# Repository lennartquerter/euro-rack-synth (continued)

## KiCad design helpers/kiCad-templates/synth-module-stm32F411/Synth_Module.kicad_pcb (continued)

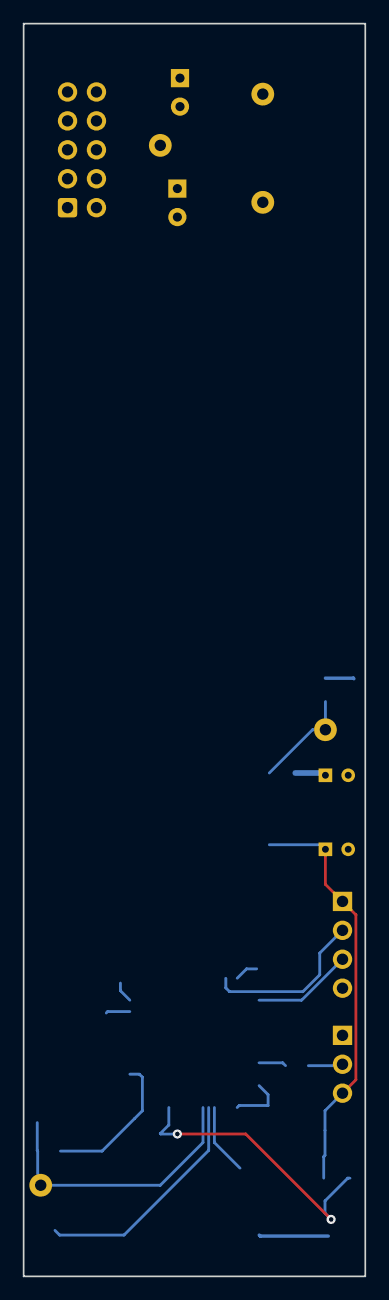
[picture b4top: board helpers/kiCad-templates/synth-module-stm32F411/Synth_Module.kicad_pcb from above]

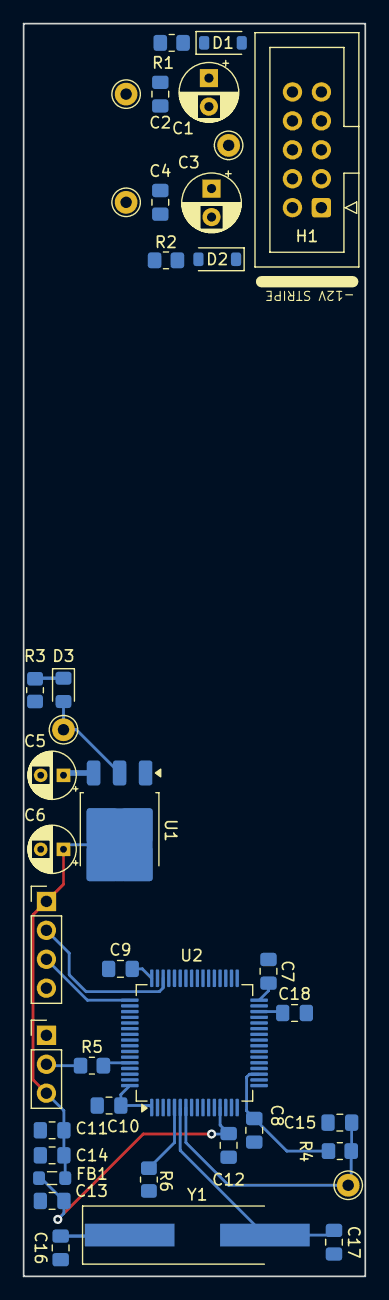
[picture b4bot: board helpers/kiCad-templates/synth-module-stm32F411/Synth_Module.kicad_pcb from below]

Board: 2 copper layers, 30.0 x 110.0 mm, 39 parts (39 on the bottom side), 19 nets.

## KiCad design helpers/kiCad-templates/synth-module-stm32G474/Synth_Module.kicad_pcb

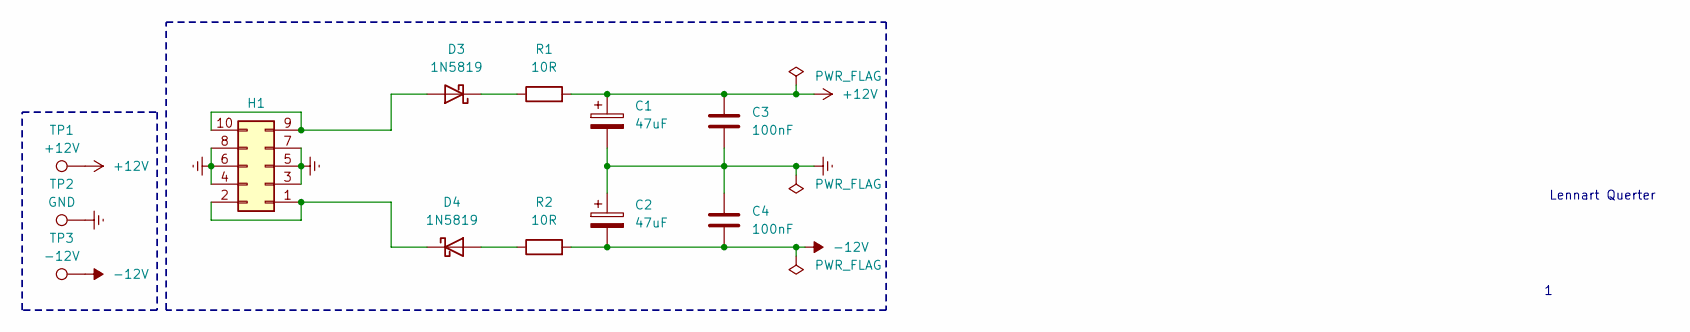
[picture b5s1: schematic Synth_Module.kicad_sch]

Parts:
C1, C2: 47uF; CP_Radial_D6.3mm_P2.50mm
C3, C4: 100nF; C_Disc_D5.0mm_W2.5mm_P5.00mm
D3, D4: 1N5819; D_DO-41_SOD81_P10.16mm_Horizontal
H1: Conn_02x05_PWR_Eurorack; IDC-Header_2x05_P2.54mm_Vertical
R1, R2: 10R; R_Axial_DIN0207_L6.3mm_D2.5mm_P7.62mm_Horizontal
TP1: +12V; Pin_D1.0mm_L10.0mm
TP2: GND; Pin_D1.0mm_L10.0mm
TP3: -12V; Pin_D1.0mm_L10.0mm

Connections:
+12V: C1.1, C3.1, R1.2, TP1.1
-12V: C2.2, C4.2, R2.2, TP3.1
GNDREF: C1.2, C2.1, C3.2, C4.1, H1.3, H1.4, H1.5, H1.6, H1.7, H1.8, TP2.1
unnamed: D3.2 (A), H1.9, H1.10
unnamed: D3.1 (K), R1.1
unnamed: D4.2 (A), R2.1
unnamed: D4.1 (K), H1.1, H1.2

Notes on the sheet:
Lennart Querter

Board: 2 copper layers, 12 parts (0 on the bottom side), 7 nets, no tracks yet.

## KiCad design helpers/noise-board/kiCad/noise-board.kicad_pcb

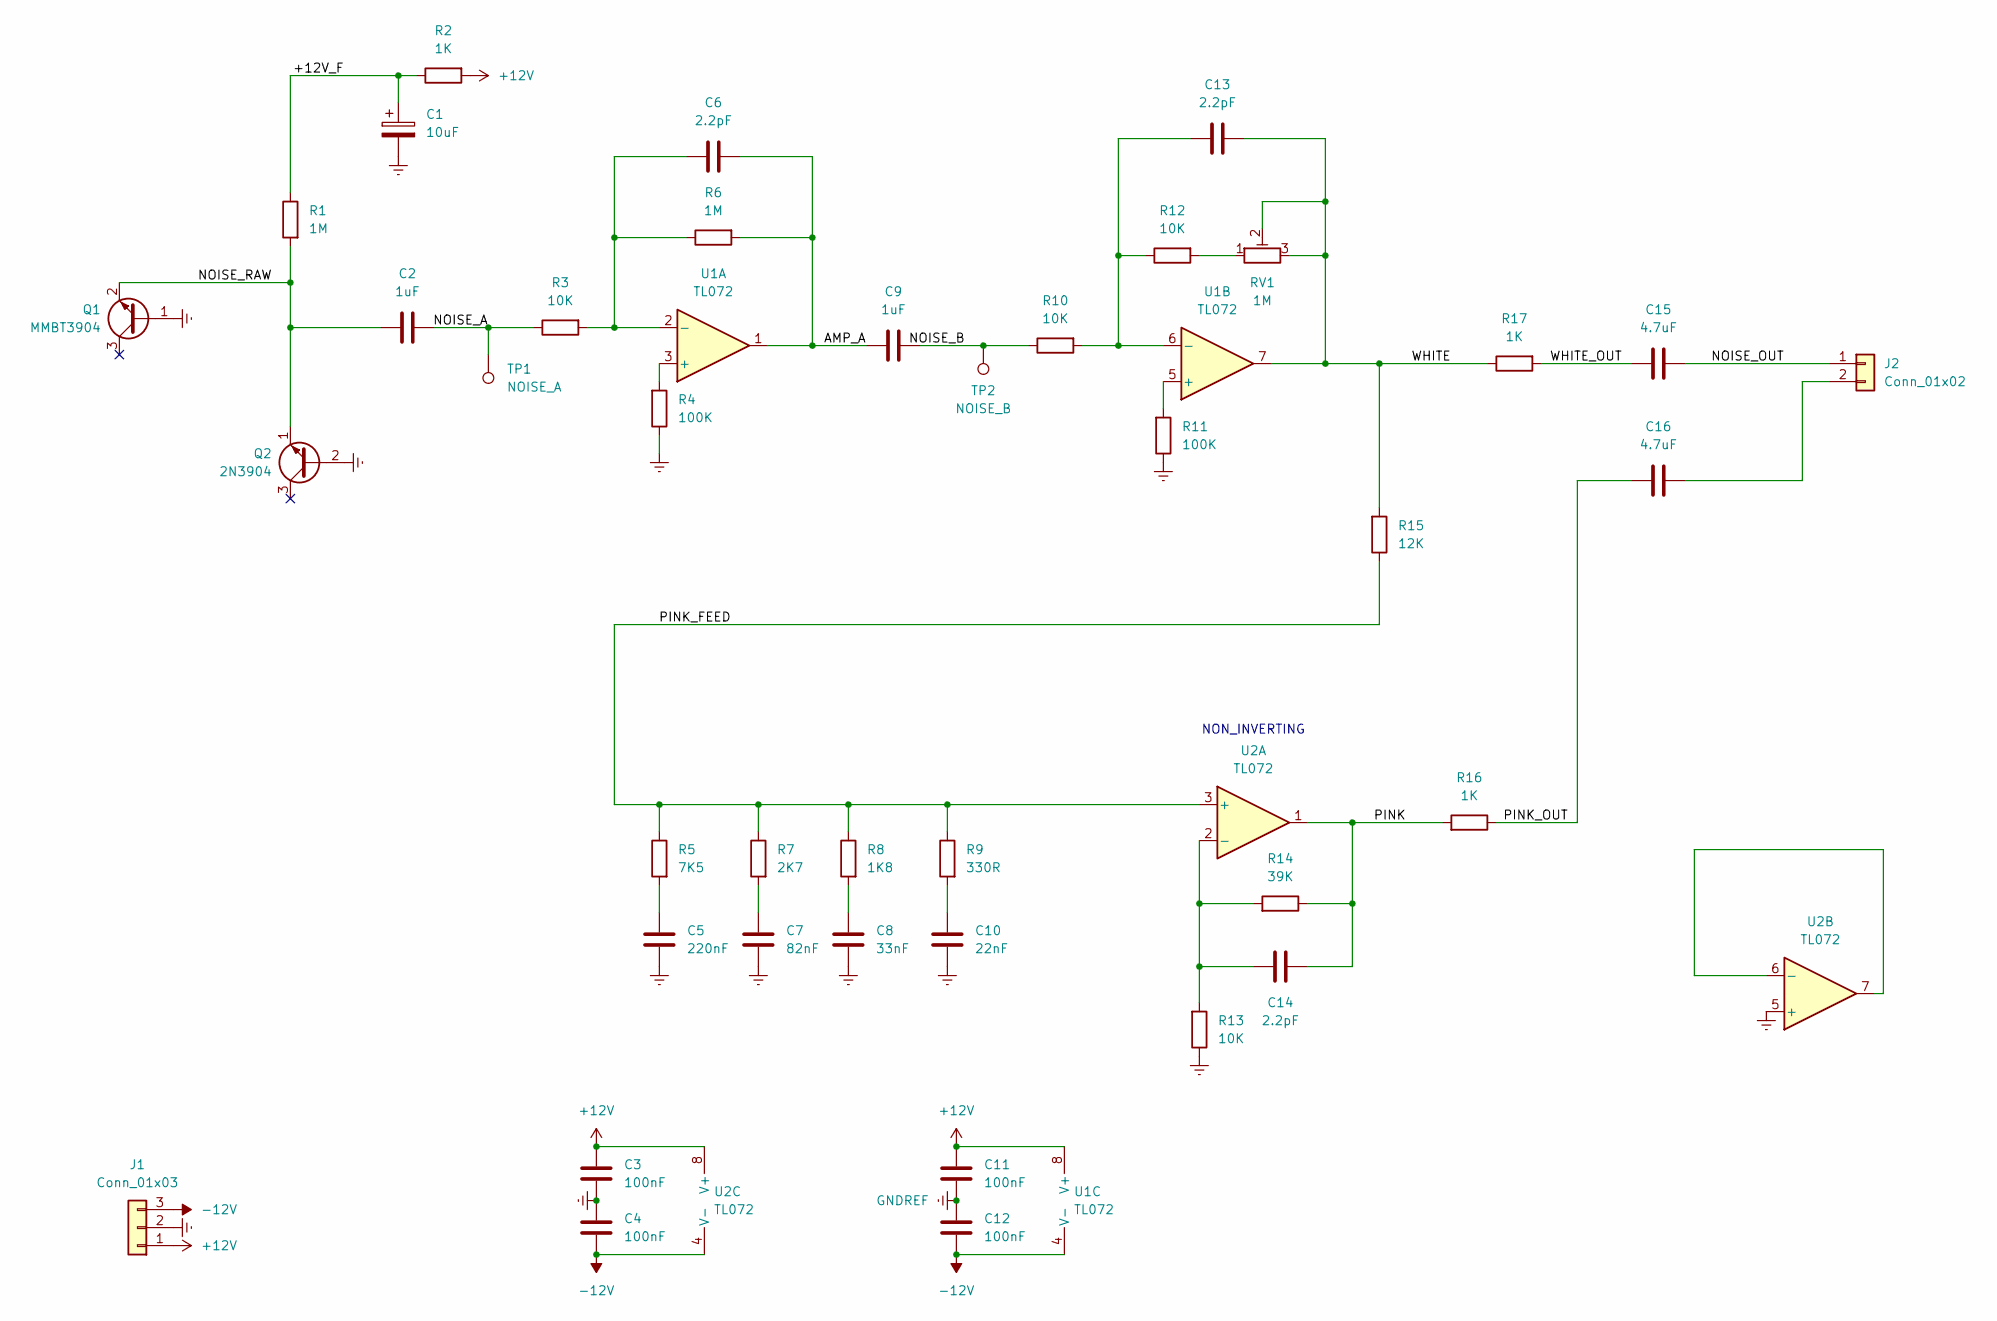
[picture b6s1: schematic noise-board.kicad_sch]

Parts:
C1: 10uF; CP_Radial_D4.0mm_P2.00mm
C2, C9: 1uF; C_0805_2012Metric_Pad1.18x1.45mm_HandSolder
C3, C4, C11, C12: 100nF; C_0805_2012Metric_Pad1.18x1.45mm_HandSolder
C5: 220nF; C_0805_2012Metric_Pad1.18x1.45mm_HandSolder
C6, C13, C14: 2.2pF; C_0805_2012Metric_Pad1.18x1.45mm_HandSolder
C7: 82nF; C_0805_2012Metric_Pad1.18x1.45mm_HandSolder
C8: 33nF; C_0805_2012Metric_Pad1.18x1.45mm_HandSolder
C10: 22nF; C_0805_2012Metric_Pad1.18x1.45mm_HandSolder
C15, C16: 4.7uF; C_0805_2012Metric_Pad1.18x1.45mm_HandSolder
J1: Conn_01x03; PinHeader_1x03_P2.54mm_Vertical
J2: Conn_01x02; PinSocket_1x02_P2.54mm_Vertical
Q1: MMBT3904; SOT-23
Q2: 2N3904; TO-92_HandSolder
R1, R6: 1M; R_0805_2012Metric_Pad1.20x1.40mm_HandSolder
R2, R16, R17: 1K; R_0805_2012Metric_Pad1.20x1.40mm_HandSolder
R3, R10, R12, R13: 10K; R_0805_2012Metric_Pad1.20x1.40mm_HandSolder
R4, R11: 100K; R_0805_2012Metric_Pad1.20x1.40mm_HandSolder
R5: 7K5; R_0805_2012Metric_Pad1.20x1.40mm_HandSolder
R7: 2K7; R_0805_2012Metric_Pad1.20x1.40mm_HandSolder
R8: 1K8; R_0805_2012Metric_Pad1.20x1.40mm_HandSolder
R9: 330R; R_0805_2012Metric_Pad1.20x1.40mm_HandSolder
R14: 39K; R_0805_2012Metric_Pad1.20x1.40mm_HandSolder
R15: 12K; R_0805_2012Metric_Pad1.20x1.40mm_HandSolder
RV1: 1M; Potentiometer_Runtron_RM-065_Vertical
TP1: NOISE_A; TestPoint_Loop_D2.54mm_Drill1.5mm_Beaded
TP2: NOISE_B; TestPoint_Loop_D2.54mm_Drill1.5mm_Beaded
U1, U2: TL072; SOIC-8

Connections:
+12V: C3.1, C11.1, J1.1, R2.1, U1.8 (V+), U2.8 (V+)
-12V: C4.2, C12.2, J1.3, U1.4 (V-), U2.4 (V-)
/+12V_F: C1.1, R1.2, R2.2
/AMP_A: C6.2, C9.1, R6.1, U1.1
/NOISE_A: C2.2, R3.2, TP1.1 (1_1)
/NOISE_B: C9.2, R10.2, TP2.1 (1_1)
/NOISE_OUT: C15.2, J2.1
/NOISE_RAW: C2.1, Q1.2 (E), Q2.1 (E), R1.1
/PINK: C14.2, R14.2, R16.1, U2.1
/PINK_FEED: R5.2, R7.2, R8.2, R9.2, R15.2, U2.3 (+)
/PINK_OUT: C16.1, R16.2
/WHITE: C13.2, R15.1, R17.2, RV1.2, RV1.3, U1.7
/WHITE_OUT: C15.1, R17.1
GNDREF: C1.2, C3.2, C4.1, C5.1, C7.1, C8.1, C10.1, C11.2, C12.1, J1.2, Q1.1 (B), Q2.2 (B), R4.2, R11.2, R13.2, U2.5 (+)
unnamed: C5.2, R5.1
unnamed: C7.2, R7.1
unnamed: C8.2, R8.1
unnamed: C10.2, R9.1
unnamed: C16.2, J2.2
unnamed: R12.1, RV1.1
unnamed: R4.1, U1.3 (+)
unnamed: C6.1, R3.1, R6.2, U1.2 (-)
unnamed: R11.1, U1.5 (+)
unnamed: C13.1, R10.1, R12.2, U1.6 (-)
unnamed: C14.1, R13.1, R14.1, U2.2 (-)
unnamed: U2.6 (-), U2.7

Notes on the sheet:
NON_INVERTING

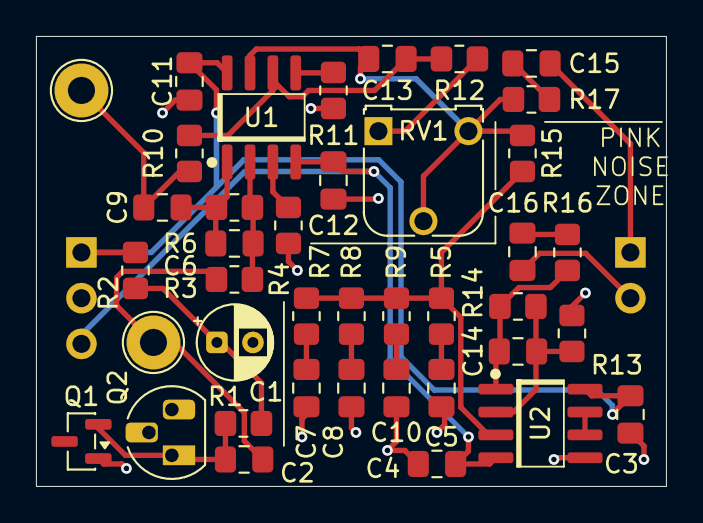
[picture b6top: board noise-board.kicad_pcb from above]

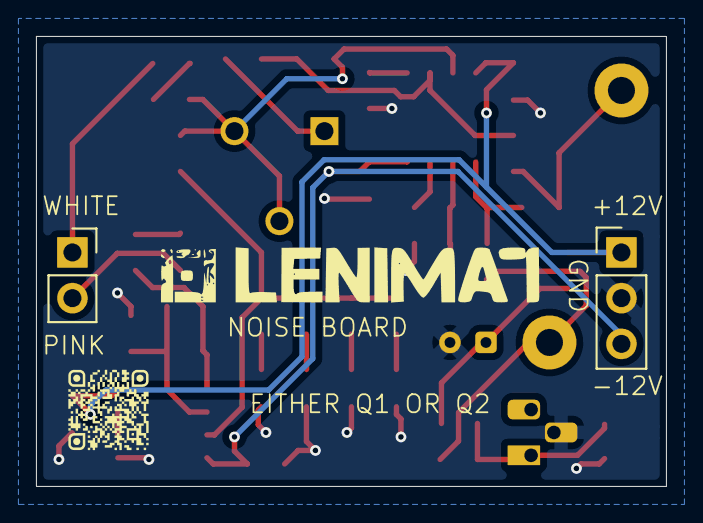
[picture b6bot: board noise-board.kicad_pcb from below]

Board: 2 copper layers, 35.0 x 25.0 mm, 42 parts (2 on the bottom side), 26 nets.

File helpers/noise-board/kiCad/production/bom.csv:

Designator,Footprint,Quantity,Value,LCSC Part #
C1,CP_Radial_D4.0mm_P2.00mm,1,10uF,
C10,0805,1,22nF,
"C11, C12, C3, C4",0805,4,100nF,
"C13, C14, C6",0805,3,2.2pF,
"C15, C16",0805,2,4.7uF,
"C2, C9",0805,2,1uF,
C5,0805,1,220nF,
C7,0805,1,82nF,
C8,0805,1,33nF,
J1,PinHeader_1x03_P2.54mm_Vertical,1,Conn_01x03,
J2,PinSocket_1x02_P2.54mm_Vertical,1,Conn_01x02,
Q1,SOT-23,1,MMBT3904,
Q2,TO-92_HandSolder,1,2N3904,
"R1, R6",0805,2,1M,
"R10, R12, R13, R3",0805,4,10K,
"R11, R4",0805,2,100K,
R14,0805,1,39K,
R15,0805,1,12K,
"R16, R17, R2",0805,3,1K,
R5,0805,1,7K5,
R7,0805,1,2K7,
R8,0805,1,1K8,
R9,0805,1,330R,
RV1,Potentiometer_Runtron_RM-065_Vertical,1,1M,
TP1,TestPoint_Loop_D2.54mm_Drill1.5mm_Beaded,1,NOISE_A,
TP2,TestPoint_Loop_D2.54mm_Drill1.5mm_Beaded,1,NOISE_B,
"U1, U2",SOIC-8,2,TL072,

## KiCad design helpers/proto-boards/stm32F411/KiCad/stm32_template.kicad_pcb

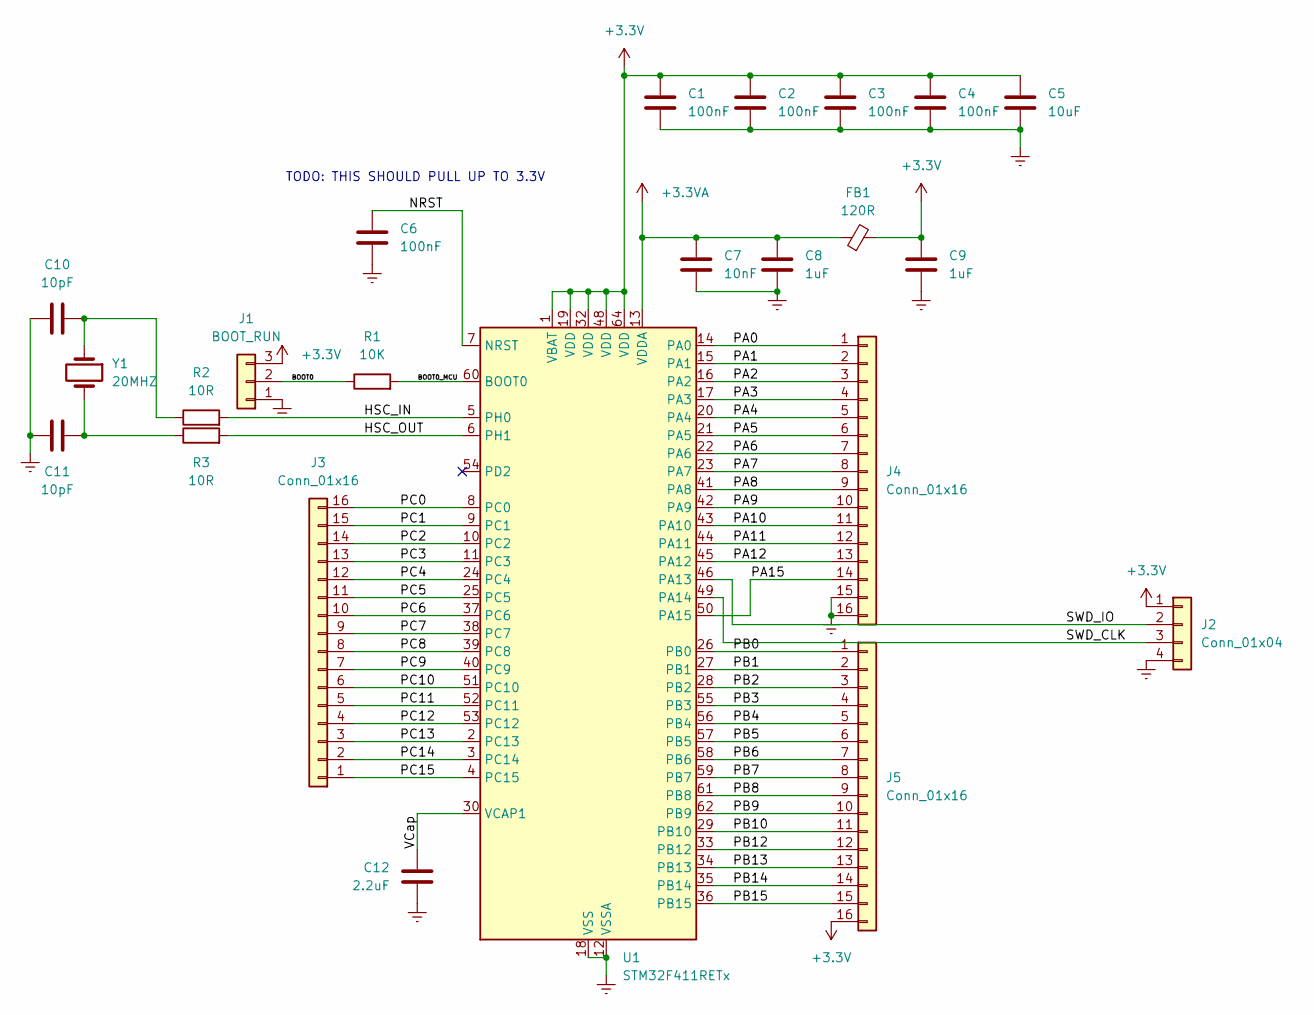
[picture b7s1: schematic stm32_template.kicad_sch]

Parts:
C1, C2, C3, C4, C6: 100nF; C_0805_2012Metric_Pad1.18x1.45mm_HandSolder
C5: 10uF; C_0805_2012Metric_Pad1.18x1.45mm_HandSolder
C7: 10nF; C_0805_2012Metric_Pad1.18x1.45mm_HandSolder
C8, C9: 1uF; C_0805_2012Metric_Pad1.18x1.45mm_HandSolder
C10, C11: 10pF; C_0805_2012Metric_Pad1.18x1.45mm_HandSolder
C12: 2.2uF; C_0805_2012Metric_Pad1.18x1.45mm_HandSolder
FB1: 120R; L_0805_2012Metric_Pad1.05x1.20mm_HandSolder
J1: BOOT_RUN; PinHeader_1x03_P2.54mm_Vertical
J2: Conn_01x04; PinHeader_1x04_P2.54mm_Vertical
J3, J4, J5: Conn_01x16; PinHeader_1x16_P2.54mm_Vertical
R1: 10K; R_0805_2012Metric_Pad1.20x1.40mm_HandSolder
R2, R3: 10R; R_0805_2012Metric_Pad1.20x1.40mm_HandSolder
U1: STM32F411RETx; LQFP-64_10x10mm_P0.5mm
Y1: 20MHZ; Crystal_SMD_HC49-SD_HandSoldering

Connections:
+3.3V: C1.2, C2.2, C3.2, C4.2, C5.2, C9.2, FB1.2, J1.3, J2.1, J5.16, U1.1 (VBAT), U1.19 (VDD), U1.32 (VDD), U1.48 (VDD), U1.64 (VDD)
+3.3VA: C7.2, C8.2, FB1.1, U1.13 (VDDA)
/BOOT0: J1.2, R1.1
/BOOT0_MCU: R1.2, U1.60 (BOOT0)
/HSC_IN: R2.2, U1.5 (PH0)
/HSC_OUT: R3.2, U1.6 (PH1)
/NRST: C6.1, U1.7 (NRST)
/PA0: J4.1, U1.14 (PA0)
/PA1: J4.2, U1.15 (PA1)
/PA2: J4.3, U1.16 (PA2)
/PA3: J4.4, U1.17 (PA3)
/PA4: J4.5, U1.20 (PA4)
/PA5: J4.6, U1.21 (PA5)
/PA6: J4.7, U1.22 (PA6)
/PA7: J4.8, U1.23 (PA7)
/PA8: J4.9, U1.41 (PA8)
/PA9: J4.10, U1.42 (PA9)
/PA10: J4.11, U1.43 (PA10)
/PA11: J4.12, U1.44 (PA11)
/PA12: J4.13, U1.45 (PA12)
/PA15: J4.14, U1.50 (PA15)
/PB0: J5.1, U1.26 (PB0)
/PB1: J5.2, U1.27 (PB1)
/PB2: J5.3, U1.28 (PB2)
/PB3: J5.4, U1.55 (PB3)
/PB4: J5.5, U1.56 (PB4)
/PB5: J5.6, U1.57 (PB5)
/PB6: J5.7, U1.58 (PB6)
/PB7: J5.8, U1.59 (PB7)
/PB8: J5.9, U1.61 (PB8)
/PB9: J5.10, U1.62 (PB9)
/PB10: J5.11, U1.29 (PB10)
/PB12: J5.12, U1.33 (PB12)
/PB13: J5.13, U1.34 (PB13)
/PB14: J5.14, U1.35 (PB14)
/PB15: J5.15, U1.36 (PB15)
/PC0: J3.16, U1.8 (PC0)
/PC1: J3.15, U1.9 (PC1)
/PC2: J3.14, U1.10 (PC2)
/PC3: J3.13, U1.11 (PC3)
/PC4: J3.12, U1.24 (PC4)
/PC5: J3.11, U1.25 (PC5)
/PC6: J3.10, U1.37 (PC6)
/PC7: J3.9, U1.38 (PC7)
/PC8: J3.8, U1.39 (PC8)
/PC9: J3.7, U1.40 (PC9)
/PC10: J3.6, U1.51 (PC10)
/PC11: J3.5, U1.52 (PC11)
/PC12: J3.4, U1.53 (PC12)
/PC13: J3.3, U1.2 (PC13)
/PC14: J3.2, U1.3 (PC14)
/PC15: J3.1, U1.4 (PC15)
/SWD_CLK: J2.3, U1.49 (PA14)
/SWD_IO: J2.2, U1.46 (PA13)
/VCap: C12.1, U1.30 (VCAP1)
GNDREF: C1.1, C2.1, C3.1, C4.1, C5.1, C6.2, C7.1, C8.1, C9.1, C10.2, C11.2, C12.2, J1.1, J2.4, J4.15, J4.16, U1.12 (VSSA), U1.18 (VSS), U1.31 (VSS), U1.47 (VSS), U1.63 (VSS)
unnamed: C10.1, R2.1, Y1.1
unnamed: C11.1, R3.1, Y1.2

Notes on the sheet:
TODO: THIS SHOULD PULL UP TO 3.3V

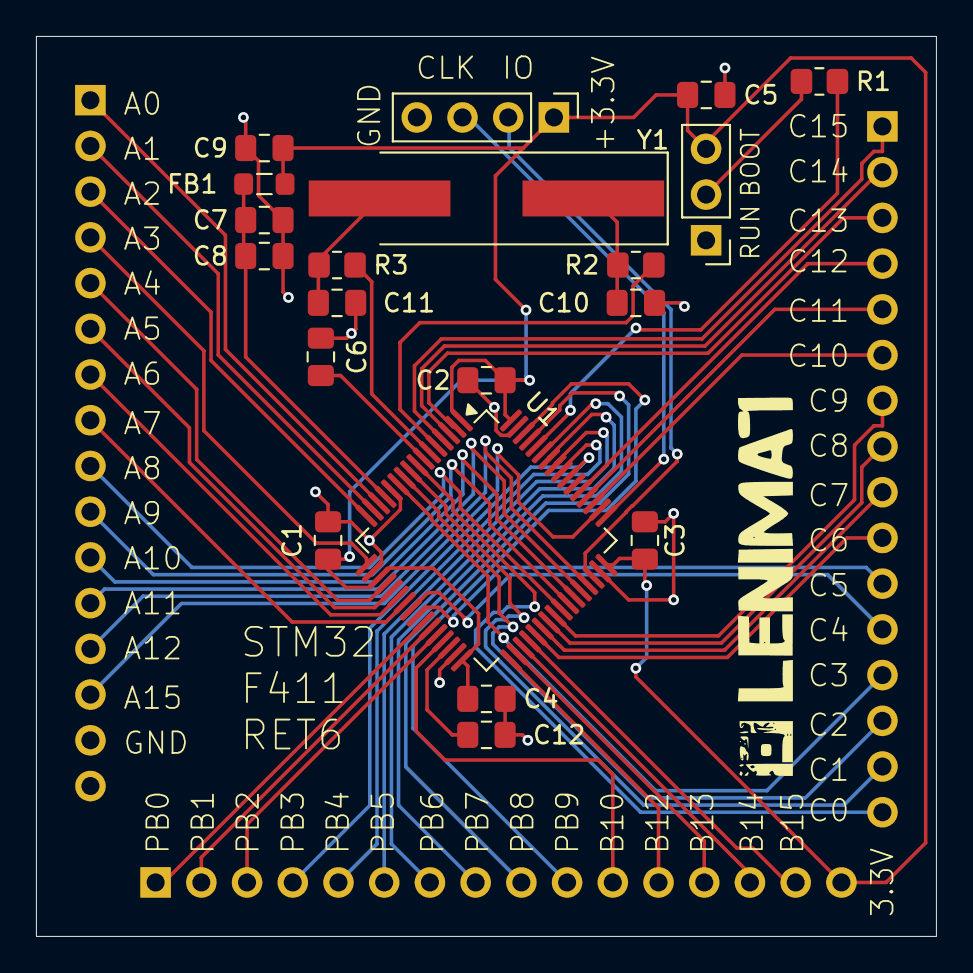
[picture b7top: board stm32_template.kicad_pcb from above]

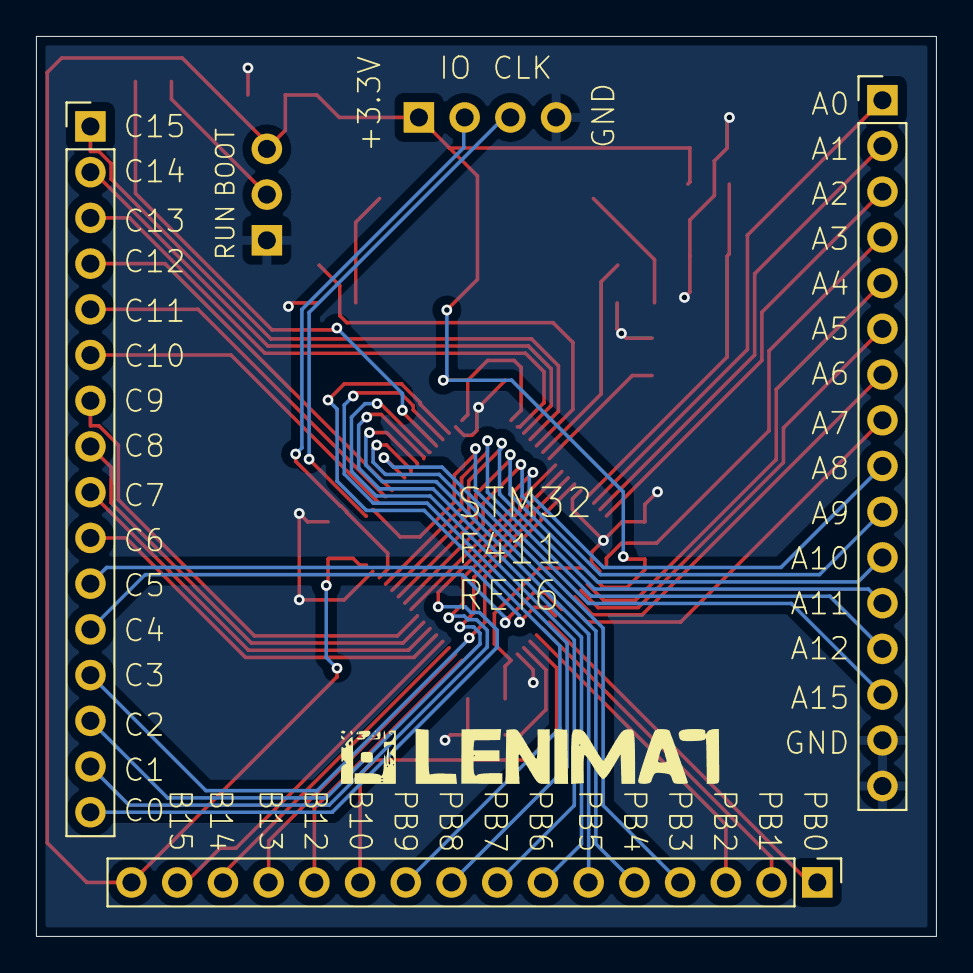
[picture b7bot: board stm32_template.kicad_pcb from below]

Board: 2 copper layers, 50.0 x 50.0 mm, 23 parts (3 on the bottom side), 58 nets.
